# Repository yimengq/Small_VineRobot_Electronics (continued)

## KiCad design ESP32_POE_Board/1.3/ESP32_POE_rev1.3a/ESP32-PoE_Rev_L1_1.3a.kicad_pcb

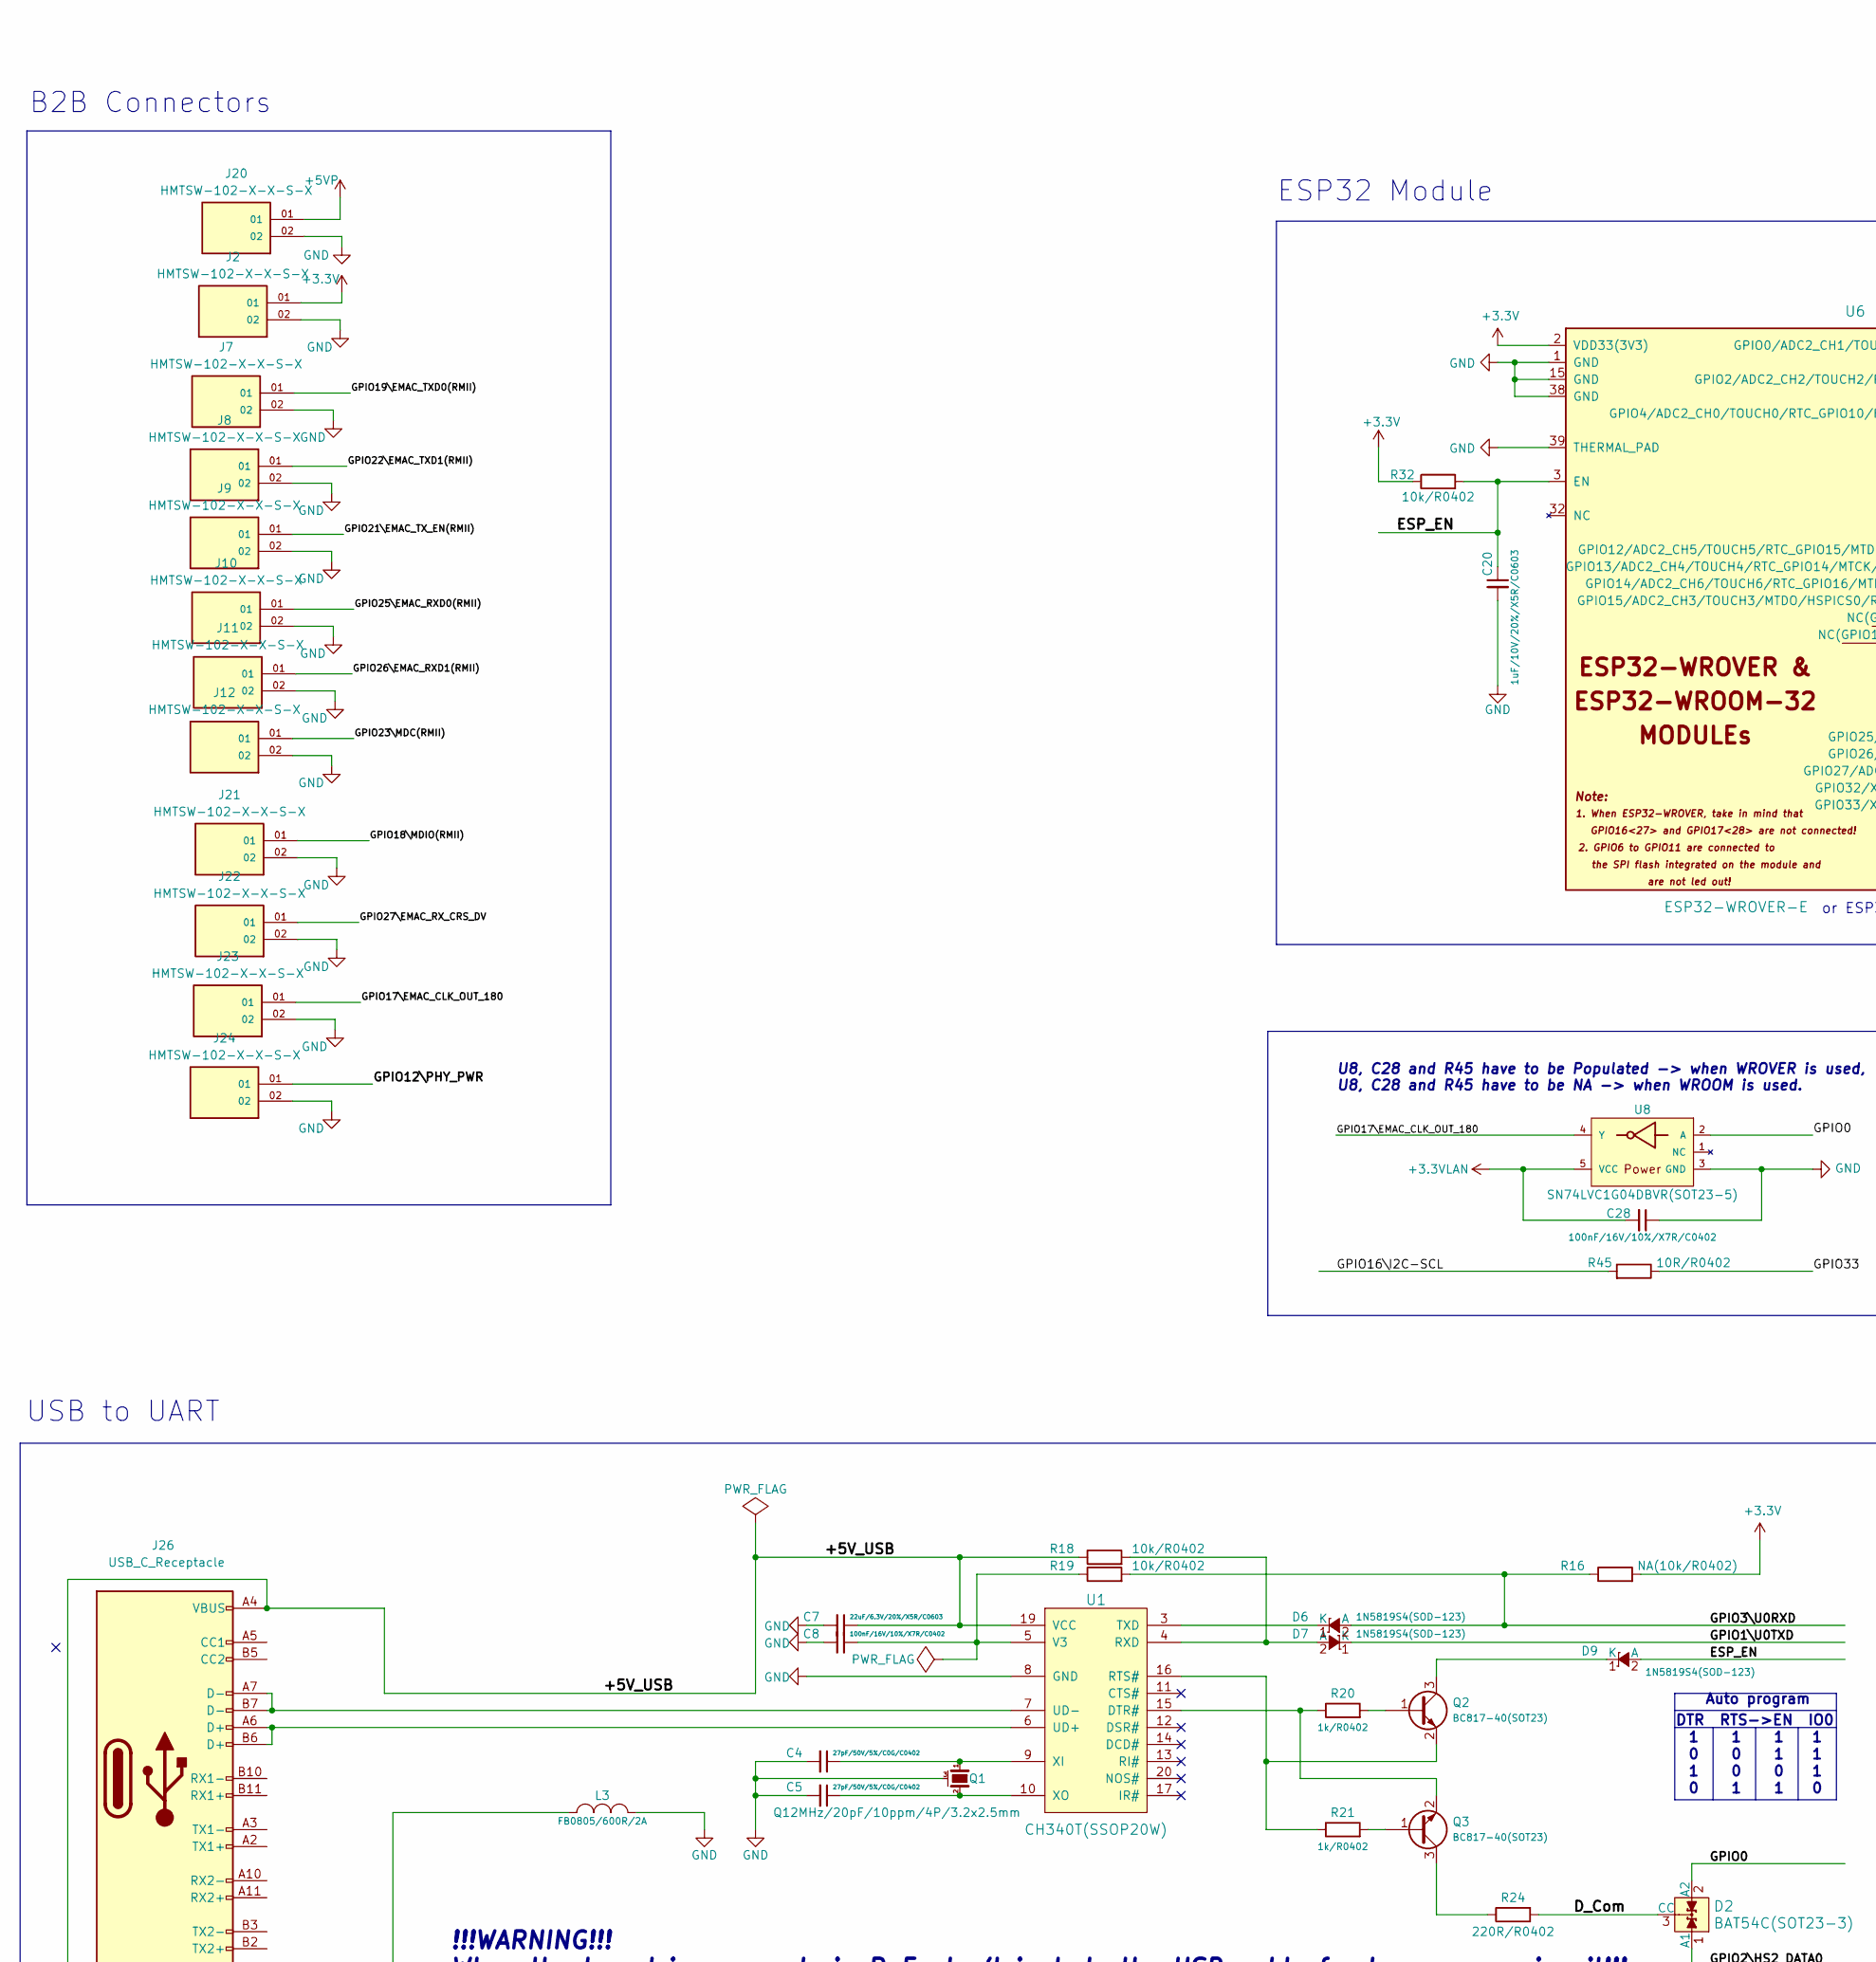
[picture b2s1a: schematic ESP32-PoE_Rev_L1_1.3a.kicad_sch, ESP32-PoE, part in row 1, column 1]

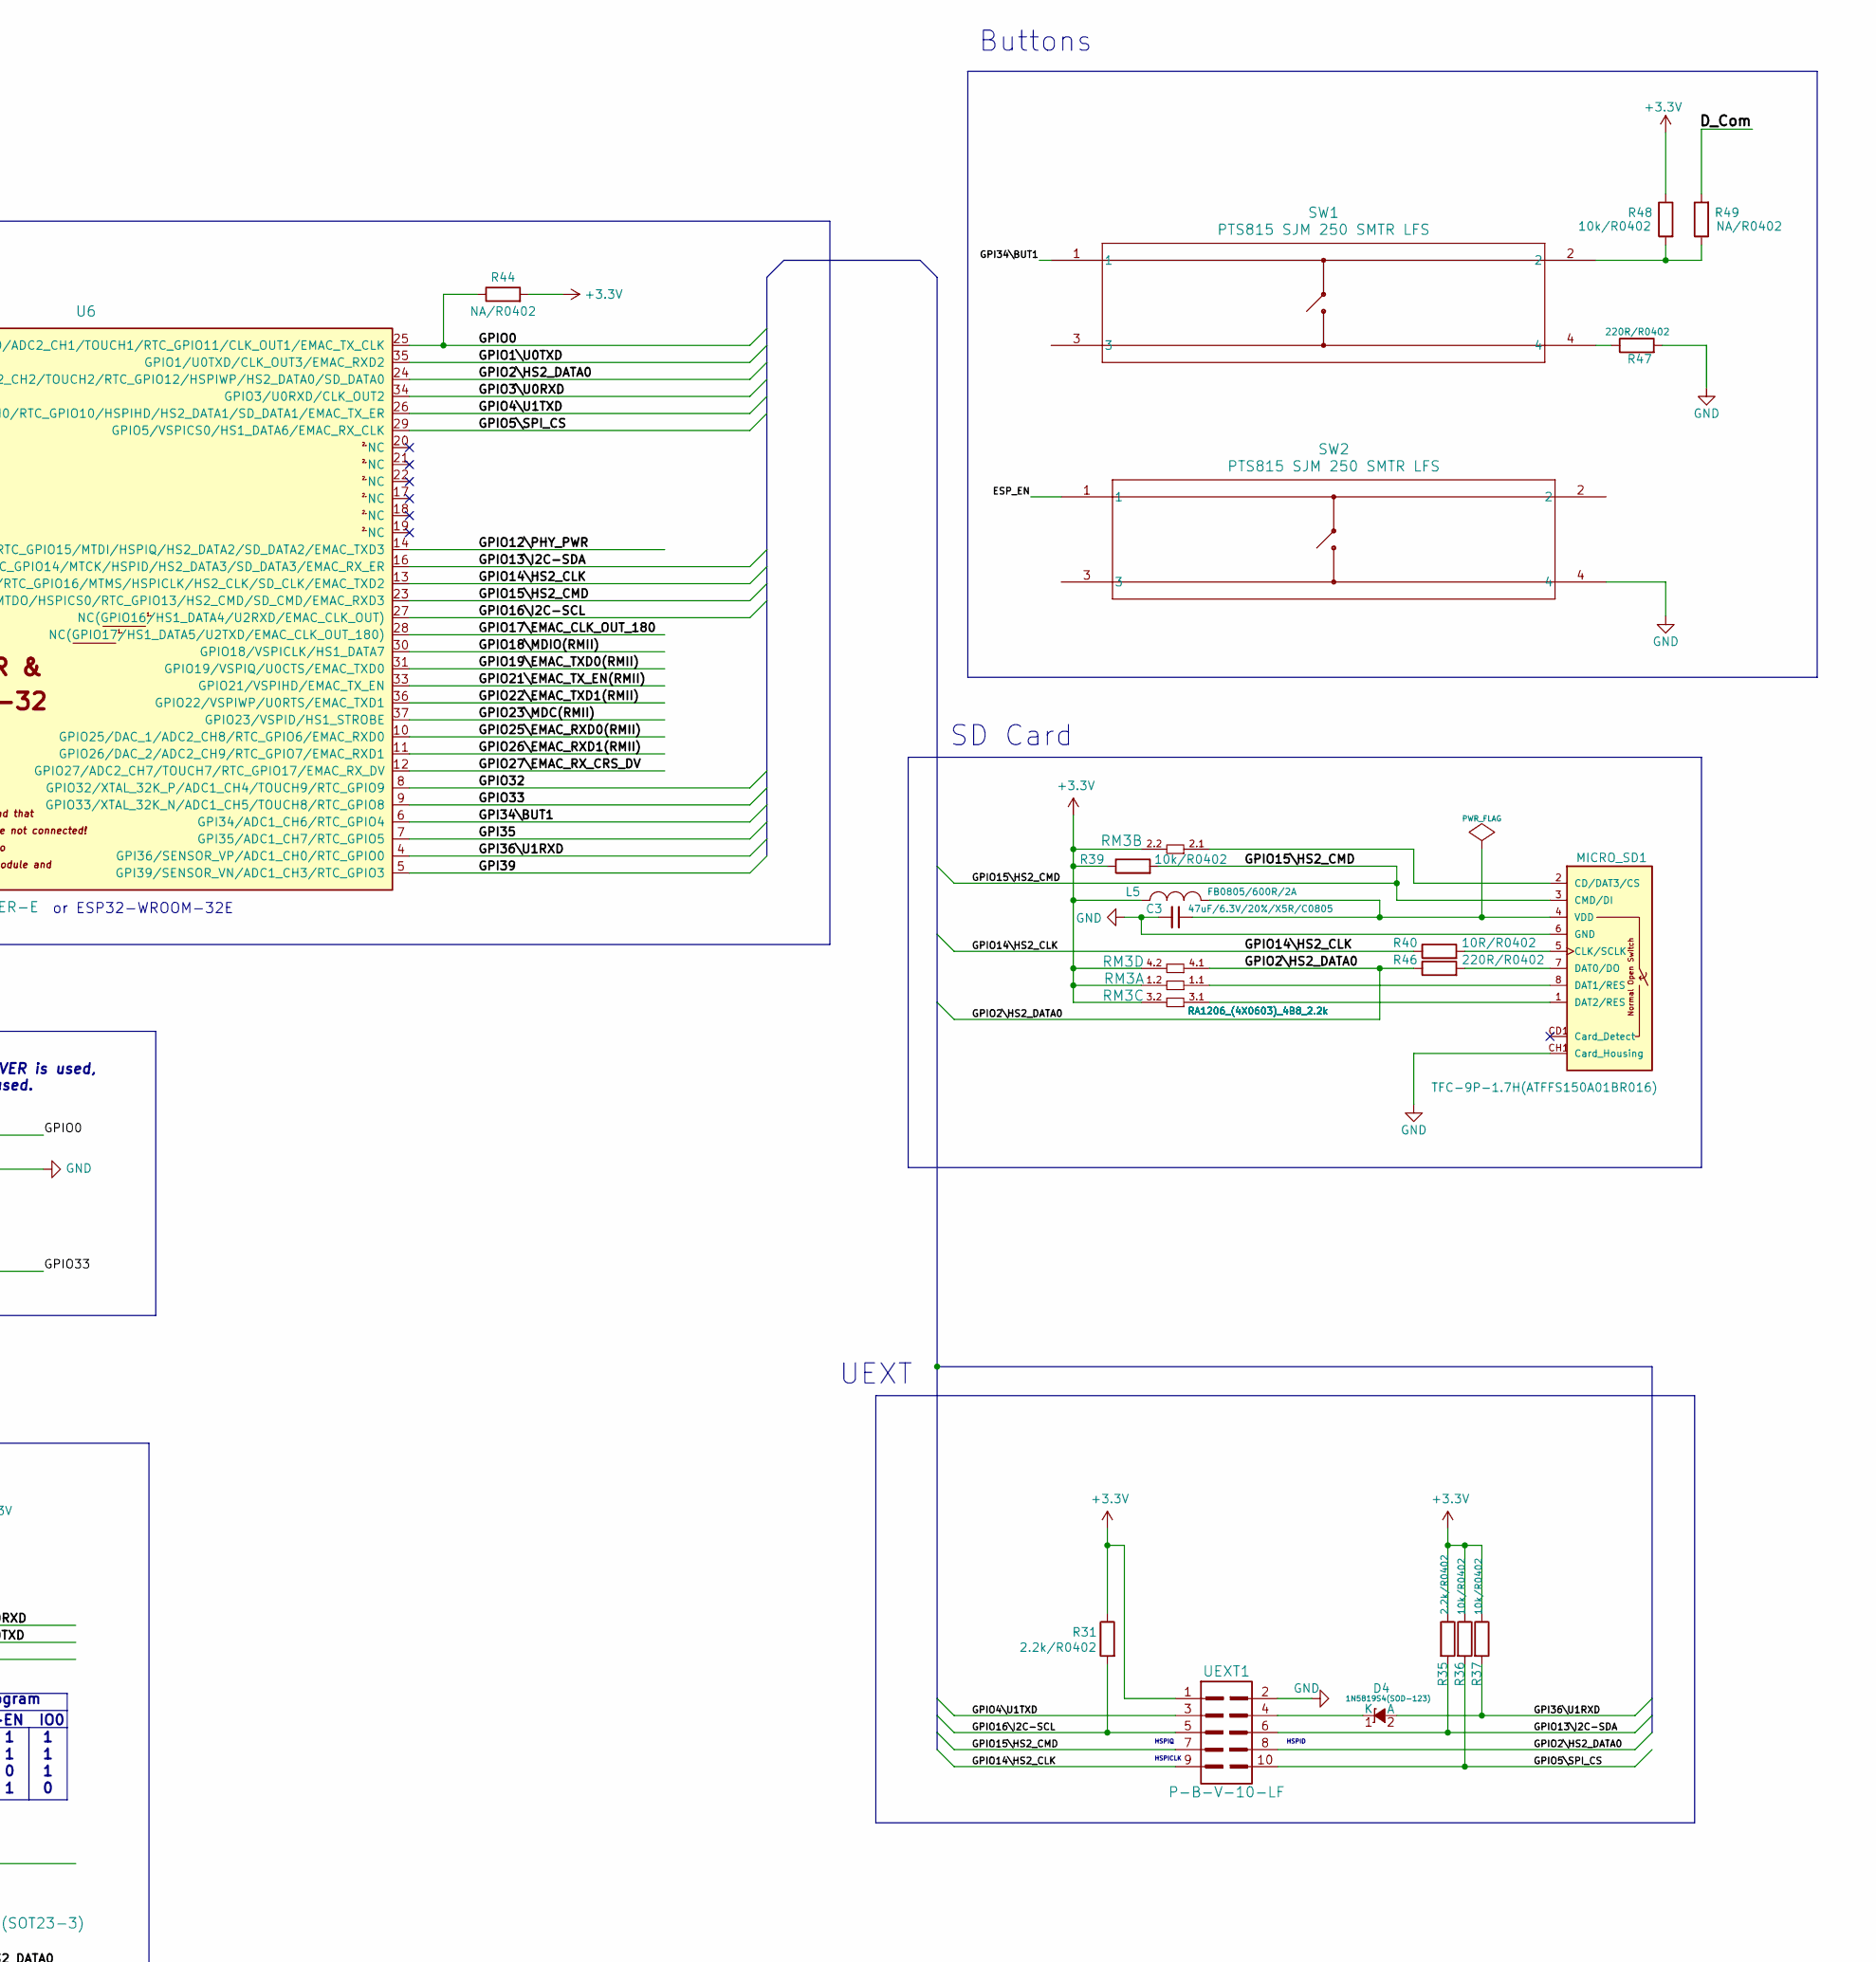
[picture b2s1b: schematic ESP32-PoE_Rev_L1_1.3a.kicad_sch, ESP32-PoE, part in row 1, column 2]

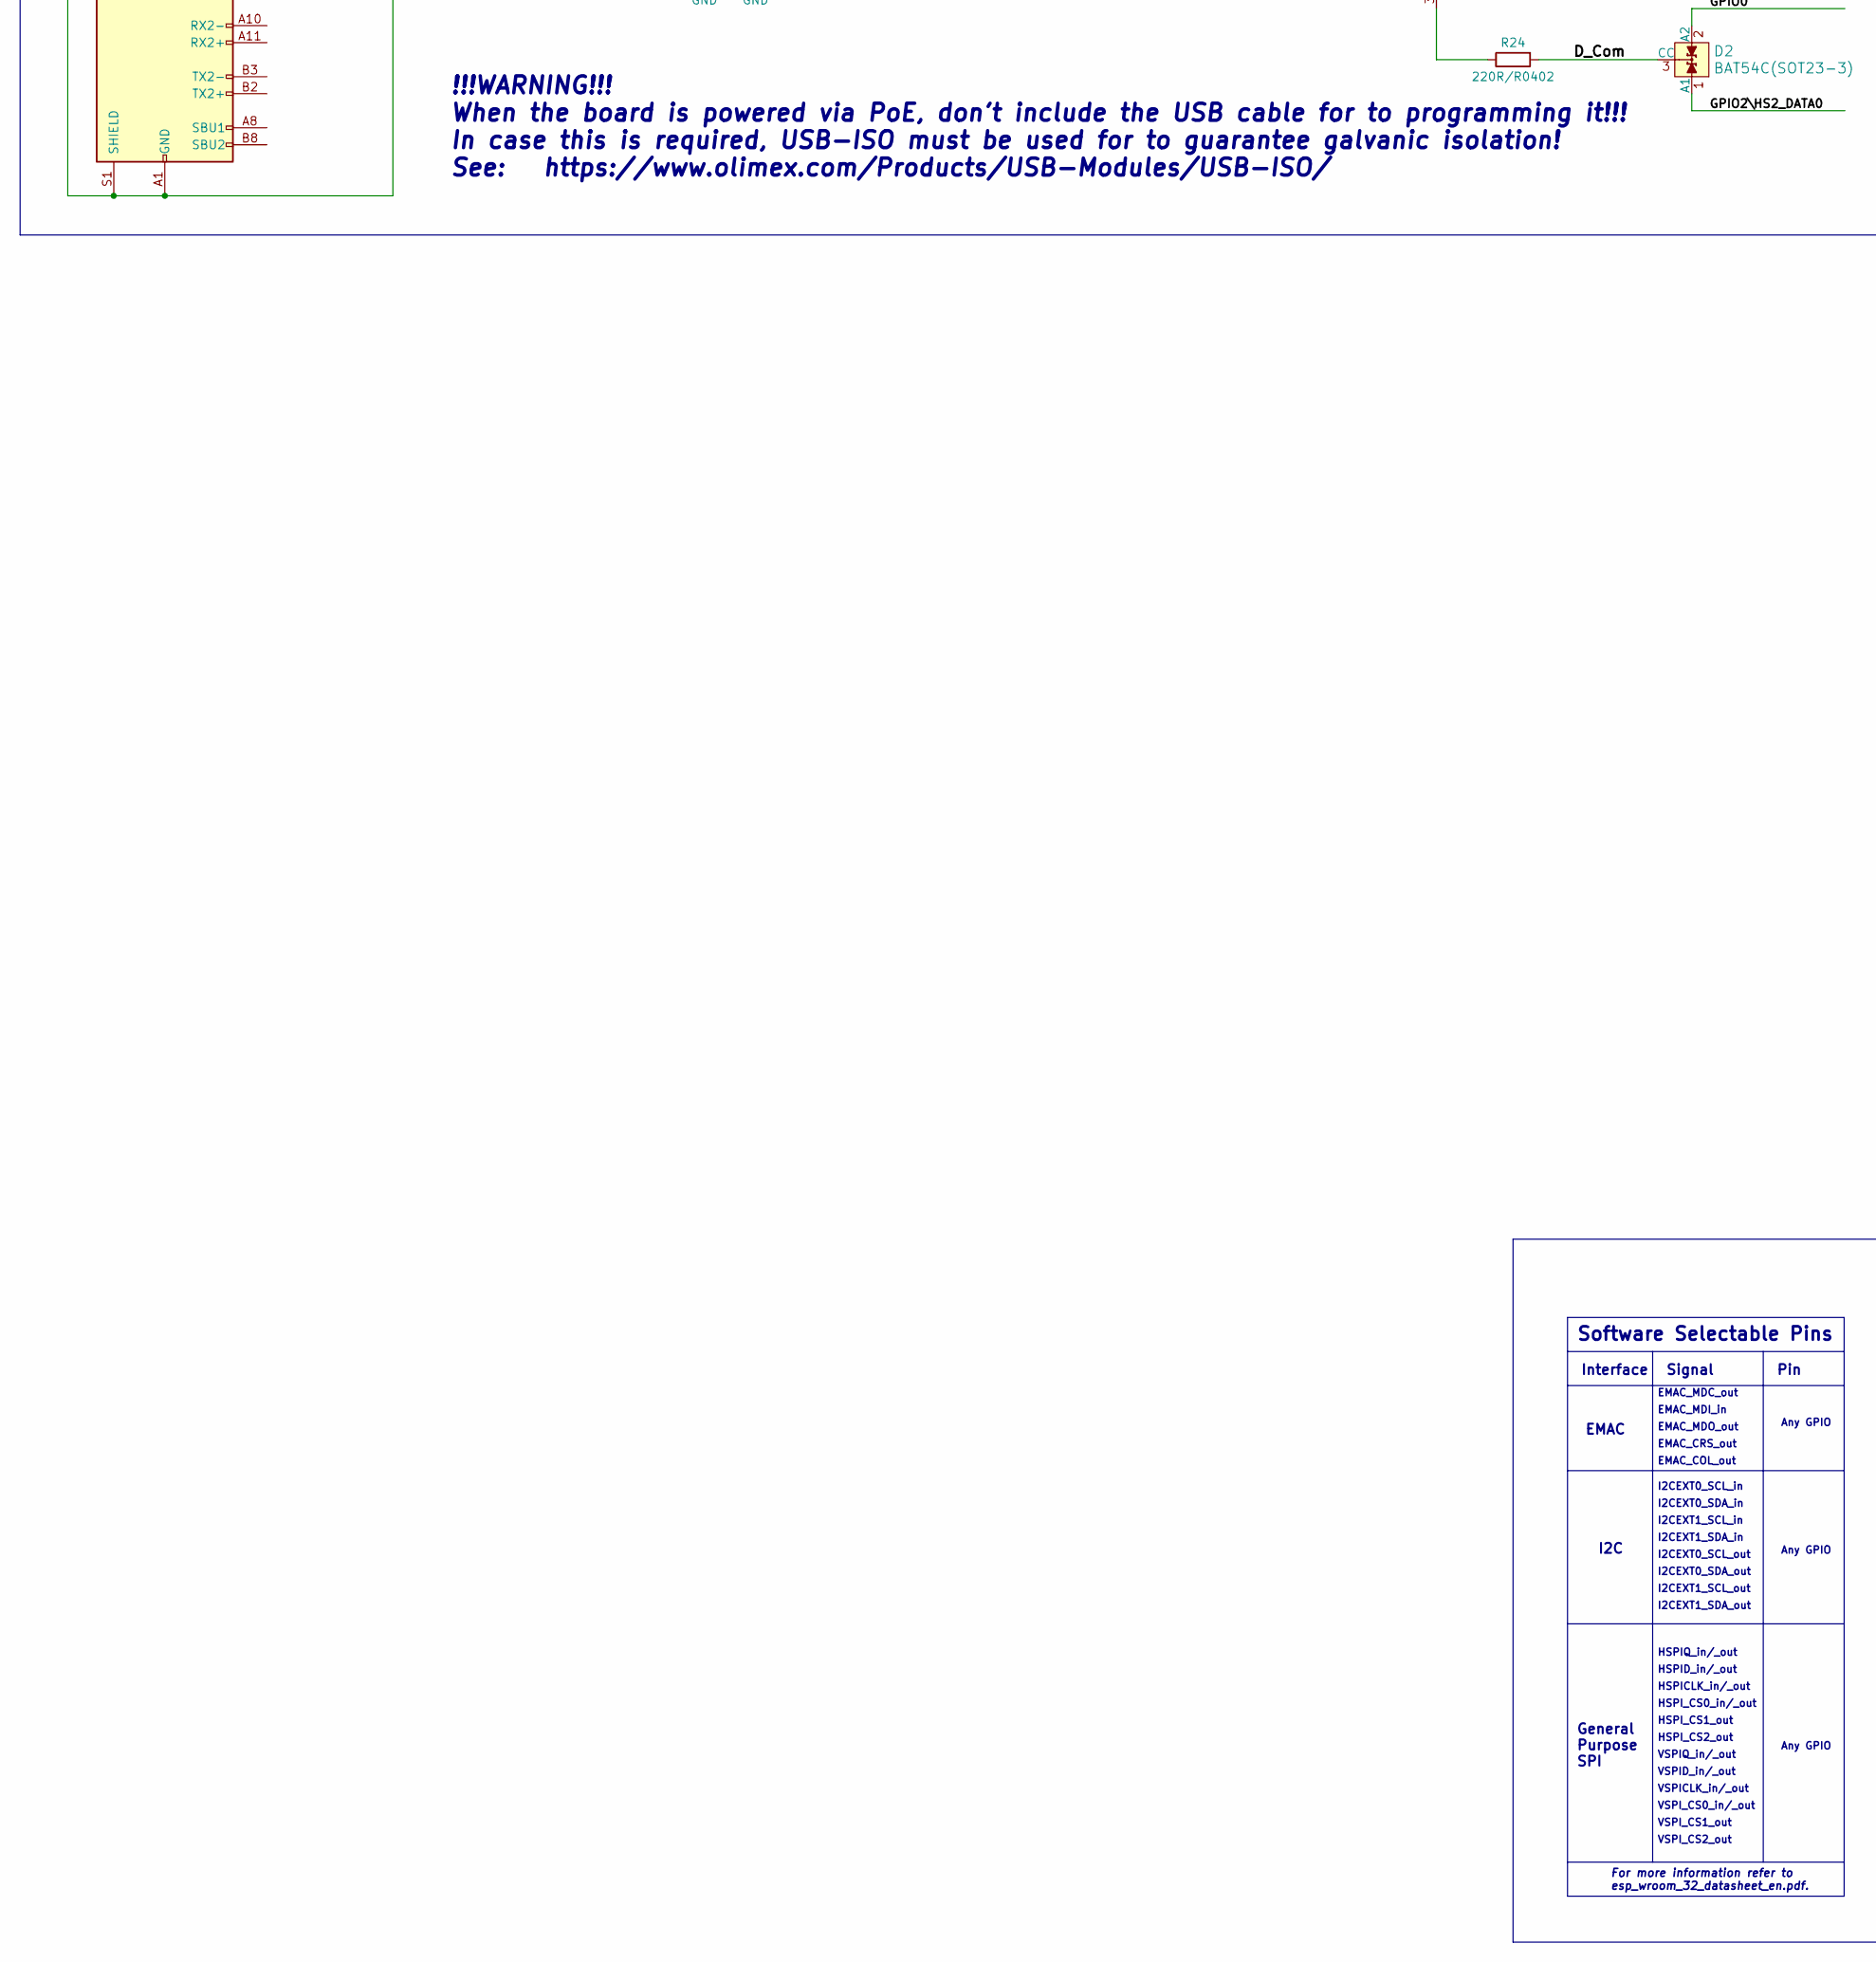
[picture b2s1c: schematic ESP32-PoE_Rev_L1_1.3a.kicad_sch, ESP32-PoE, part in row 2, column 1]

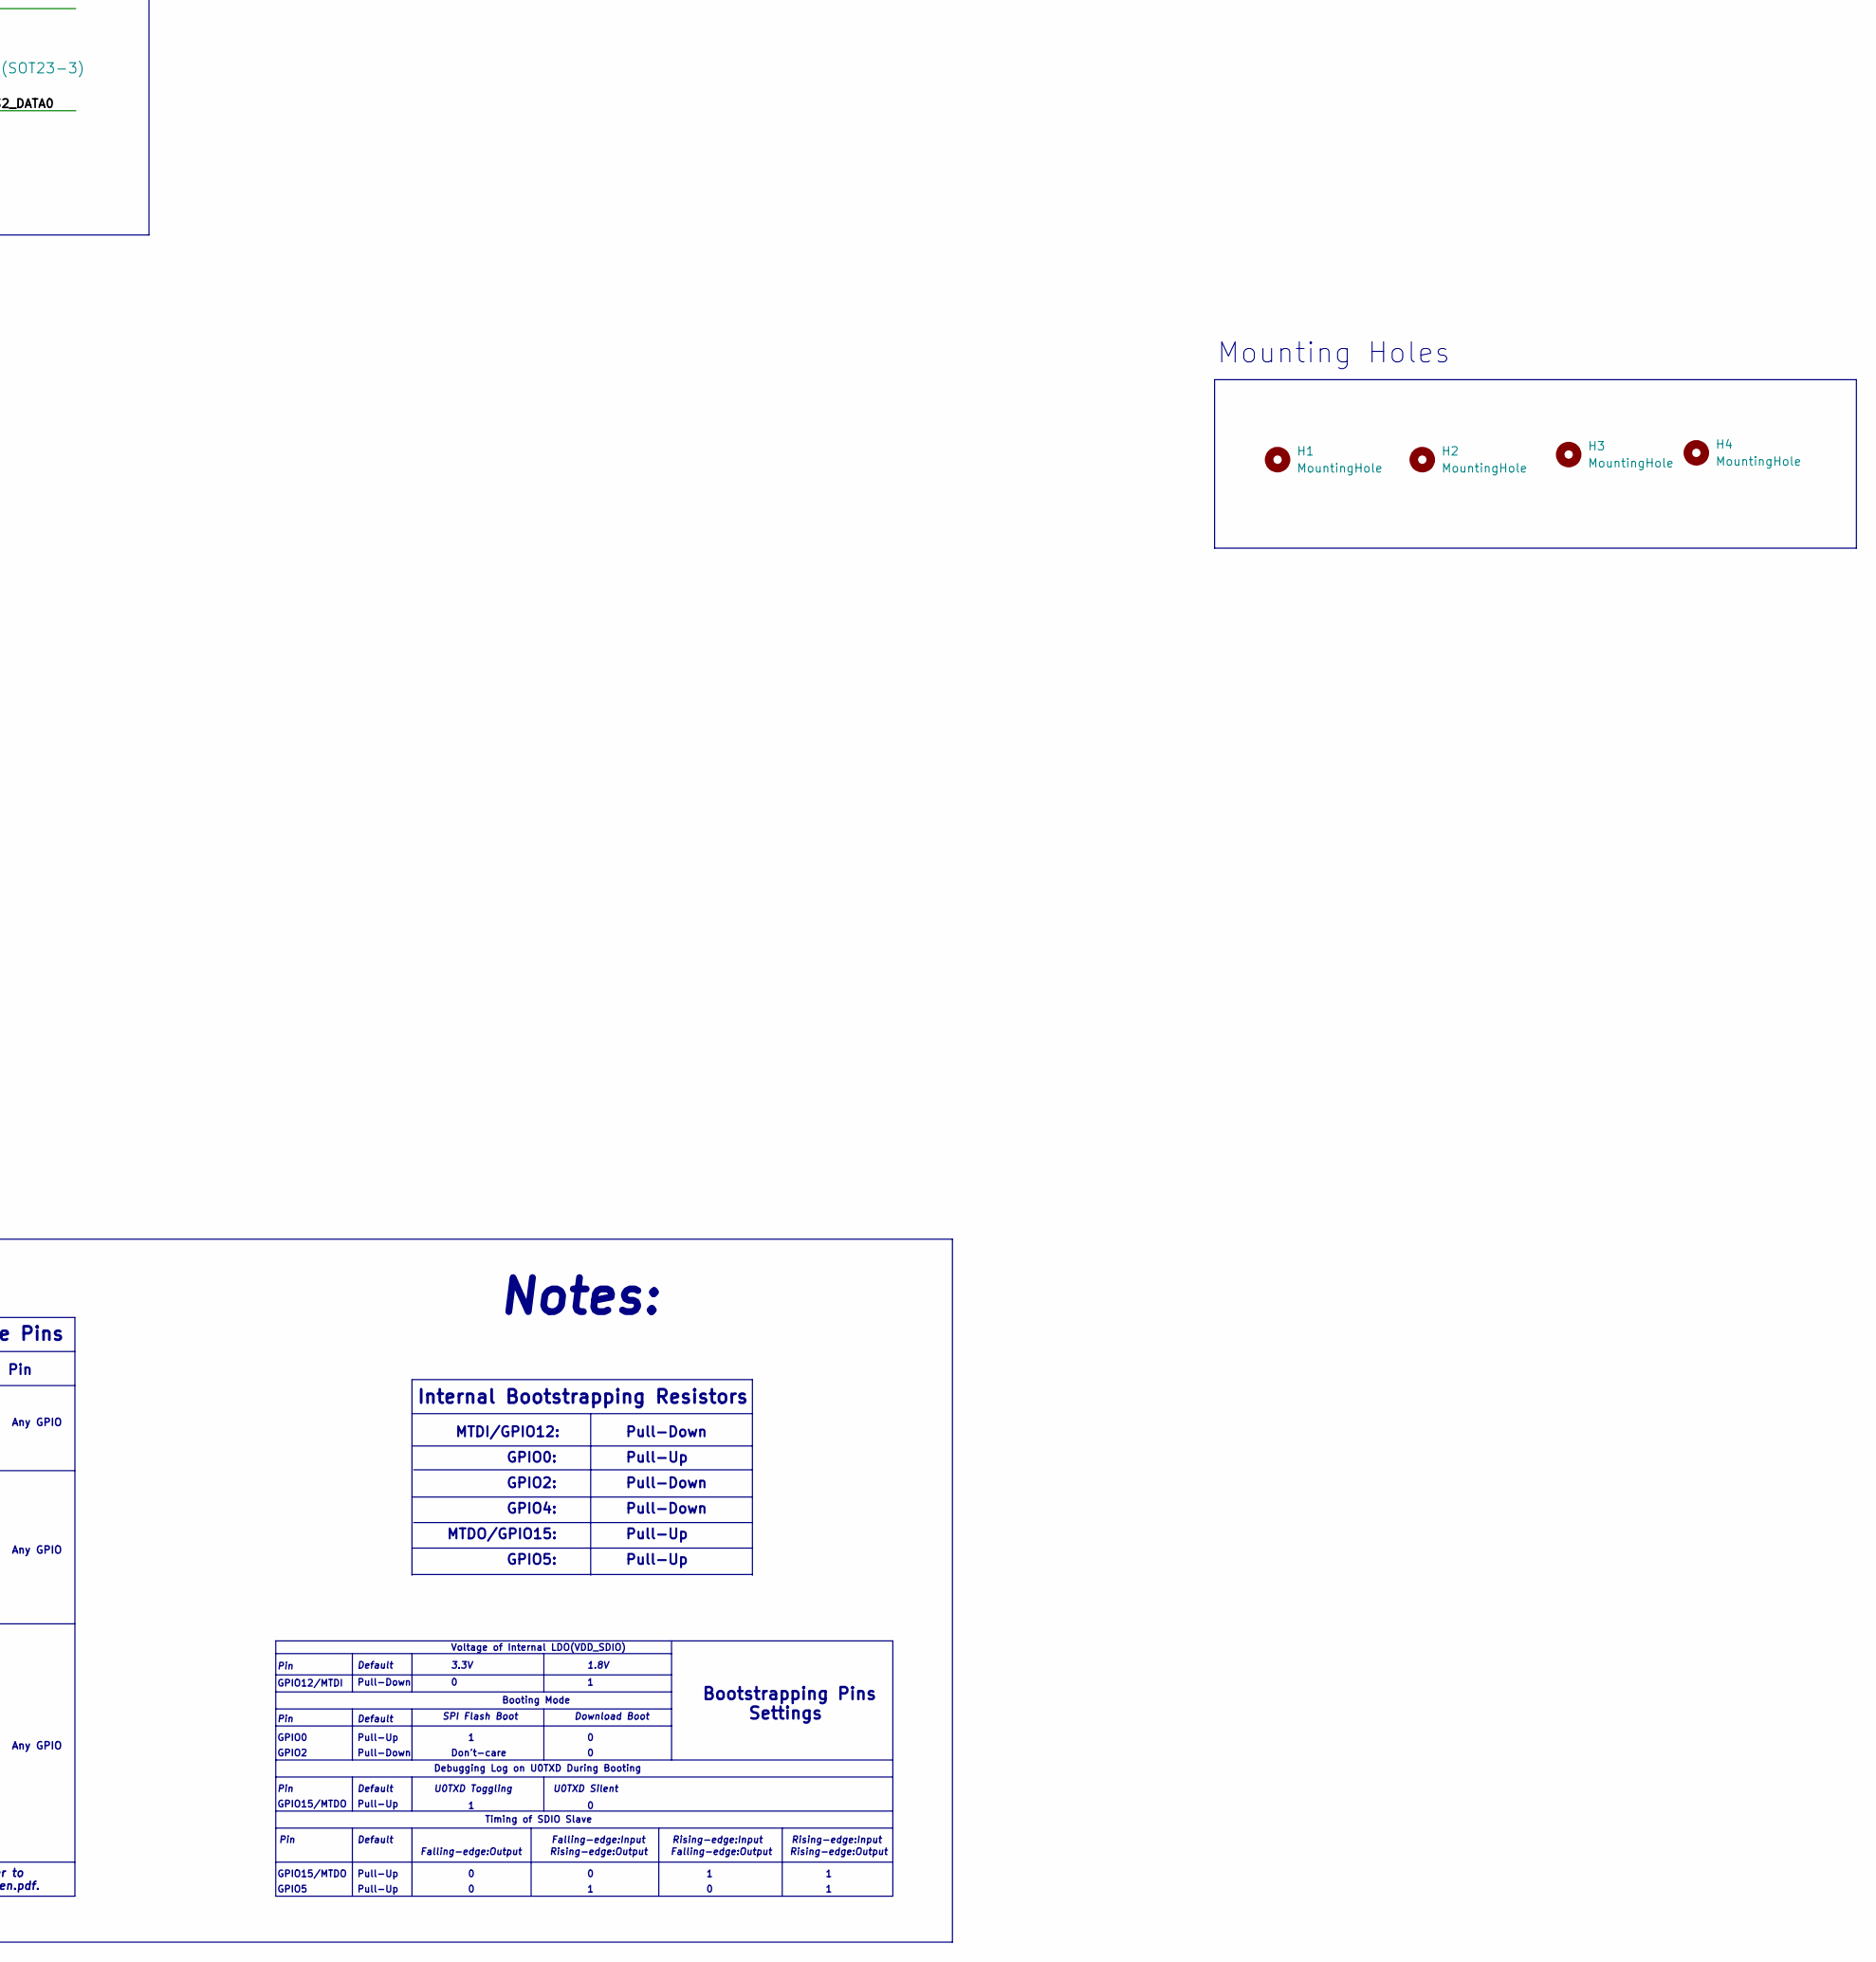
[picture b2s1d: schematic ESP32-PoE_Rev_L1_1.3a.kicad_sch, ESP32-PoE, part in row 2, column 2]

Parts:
C3: 47uF/6.3V/20%/X5R/C0805; C_0805_5MIL_DWS
C4, C5: 27pF/50V/5%/C0G/C0402; C_0402_5MIL_DWS
C7: 22uF/6.3V/20%/X5R/C0603; C_0603_5MIL_DWS
C8, C28: 100nF/16V/10%/X7R/C0402; C_0402_5MIL_DWS
C20: 1uF/10V/20%/X5R/C0603; C_0603_5MIL_DWS
D2: BAT54C(SOT23-3); SOT23-3
D4, D6, D7, D9: 1N5819S4(SOD-123); SOD-123_1C-2A_KA
H1, H2, H3, H4: MountingHole; MountingHole_2.1mm
J2, J7, J8, J9, J10, J11, J12, J20, J21, J22, J23, J24: HMTSW-102-X-X-S-X; SAMTEC_HMTSW-102-X-X-S-X; PARTREV A
J26: USB_C_Receptacle; USB_C_Receptacle_Molex_105450-0101-L
L3, L5: FB0805/600R/2A; L_0805_5MIL_DWS
MICRO_SD1: TFC-9P-1.7H(ATFFS150A01BR016); uSD(TFC-9P-1.xH(ATFFS150A01BR016))
Q1: Q12MHz/20pF/10ppm/4P/3.2x2.5mm; TSX-3.2x2.5mm_GND(3)
Q2, Q3: BC817-40(SOT23); SOT23
R16: NA(10k/R0402); R_0402_5MIL_DWS
R18, R19, R32, R36, R37, R39, R48: 10k/R0402; R_0402_5MIL_DWS
R20, R21: 1k/R0402; R_0402_5MIL_DWS
R24, R46, R47: 220R/R0402; R_0402_5MIL_DWS
R31, R35: 2.2k/R0402; R_0402_5MIL_DWS
R40, R45: 10R/R0402; R_0402_5MIL_DWS
R44, R49: NA/R0402; R_0402_5MIL_DWS
RM3: RA1206_(4X0603)_4B8_2.2k; R_MATRIX_4
SW1, SW2: PTS815 SJM 250 SMTR LFS; SW4_PTS815 SJM 250 SMTR LFS_CNK
U1: CH340T(SSOP20W); SSOP-20W
U6: ESP32-WROVER-E; ESP32-WROVER(WROOM)-UNIVERSAL_MODULE
U8: SN74LVC1G04DBVR(SOT23-5); SOT-23-5
UEXT1: P-B-V-10-LF; GBH-254-SMT-10

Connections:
+3.3V: J2.01, L5.1, R16.2, R31.1, R32.1, R35.1, R36.1, R37.1, R39.1, R44.2, R48.1, RM3.1.2, RM3.2.2, RM3.3.2, RM3.4.2, U6.2 (VDD33(3V3)), UEXT1.1
+3.3VLAN: C28.2, U8.5 (VCC)
+5VP: J20.01
/+5V_USB: C7.1, J26.A1 (GND), J26.A4 (VBUS), J26.A9 (VBUS), J26.A12 (GND), J26.B1 (GND), J26.B4 (VBUS), J26.B9 (VBUS), J26.B12 (GND), J26.S1 (SHIELD), L3.1, R18.1, U1.19 (VCC)
/D_Com: D2.3 (CC), R24.2, R49.2
/ESP_EN: C20.1, D9.2 (A), R32.2, SW2.1, U6.3 (EN)
/GPI34\BUT1: SW1.1, U6.6 (GPI34/ADC1_CH6/RTC_GPIO4)
/GPI35: U6.7 (GPI35/ADC1_CH7/RTC_GPIO5)
/GPI36\U1RXD: D4.2 (A), R37.2, U6.4 (GPI36/SENSOR_VP/ADC1_CH0/RTC_GPIO0)
/GPI39: U6.5 (GPI39/SENSOR_VN/ADC1_CH3/RTC_GPIO3)
/GPIO0: D2.2 (A2), R44.1, U6.25 (GPIO0/ADC2_CH1/TOUCH1/RTC_GPIO11/CLK_OU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), U8.2 (A)
/GPIO1\U0TXD: D7.1 (K), U6.35 (GPIO1/U0TXD/CLK_OUT3/EMAC_RXD2)
/GPIO2\HS2_DATA0: D2.1 (A1), R46.1, RM3.4.1, U6.24 (GPIO2/ADC2_CH2/TOUCH2/RTC_GPIO12/HSPIWP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), UEXT1.8
/GPIO3\U0RXD: D6.2 (A), R16.1, R19.2, U6.34 (GPIO3/U0RXD/CLK_OUT2)
/GPIO4\U1TXD: U6.26 (GPIO4/ADC2_CH0/TOUCH0/RTC_GPIO10/HSPIHD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), UEXT1.3
/GPIO5\SPI_CS: R36.2, U6.29 (GPIO5/VSPICS0/HS1_DATA6/EMAC_RX_CLK), UEXT1.10
/GPIO12\PHY_PWR: J24.01, U6.14 (GPIO12/ADC2_CH5/TOUCH5/RTC_GPIO15/MTDI/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)
/GPIO13\I2C-SDA: R35.2, U6.16 (GPIO13/ADC2_CH4/TOUCH4/RTC_GPIO14/MTCK/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), UEXT1.6
/GPIO14\HS2_CLK: R40.1, U6.13 (GPIO14/ADC2_CH6/TOUCH6/RTC_GPIO16/MTMS/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), UEXT1.9
/GPIO15\HS2_CMD: MICRO_SD1.3 (CMD/DI), R39.2, U6.23 (GPIO15/ADC2_CH3/TOUCH3/MTDO/HSPICS0/RTC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), UEXT1.7
/GPIO16\I2C-SCL: R31.2, R45.2, U6.27 (NC(GPIO16/HS1_DATA4/U2RXD/EMAC_CLK_OUT)), UEXT1.5
/GPIO17\EMAC_CLK_OUT_180: J23.01, U6.28 (NC(GPIO17/HS1_DATA5/U2TXD/EMAC_CLK_OUT_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), U8.4 (Y)
/GPIO18\MDIO(RMII): J21.01, U6.30 (GPIO18/VSPICLK/HS1_DATA7)
/GPIO19\EMAC_TXD0(RMII): J7.01, U6.31 (GPIO19/VSPIQ/U0CTS/EMAC_TXD0)
/GPIO21\EMAC_TX_EN(RMII): J9.01, U6.33 (GPIO21/VSPIHD/EMAC_TX_EN)
/GPIO22\EMAC_TXD1(RMII): J8.01, U6.36 (GPIO22/VSPIWP/U0RTS/EMAC_TXD1)
/GPIO23\MDC(RMII): J12.01, U6.37 (GPIO23/VSPID/HS1_STROBE)
/GPIO25\EMAC_RXD0(RMII): J10.01, U6.10 (GPIO25/DAC_1/ADC2_CH8/RTC_GPIO6/EMAC_RX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)
/GPIO26\EMAC_RXD1(RMII): J11.01, U6.11 (GPIO26/DAC_2/ADC2_CH9/RTC_GPIO7/EMAC_RX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)
/GPIO27\EMAC_RX_CRS_DV: J22.01, U6.12 (GPIO27/ADC2_CH7/TOUCH7/RTC_GPIO17/EMAC_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)
/GPIO32: U6.8 (GPIO32/XTAL_32K_P/ADC1_CH4/TOUCH9/RTC_G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)
/GPIO33: R45.1, U6.9 (GPIO33/XTAL_32K_N/ADC1_CH5/TOUCH8/RTC_G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)
GND: C3.2, C4.2, C5.2, C7.2, C8.2, C20.2, C28.1, J2.02, J7.02, J8.02, J9.02, J10.02, J11.02, J12.02, J20.02, J21.02, J22.02, J23.02, J24.02, L3.2, MICRO_SD1.6 (GND), MICRO_SD1.CH1 (Card_Housing), Q1.3 (case), R47.2, SW2.4, U1.8 (GND), U6.1 (GND), U6.15 (GND), U6.38 (GND), U6.39 (THERMAL_PAD), U8.3 (GND), UEXT1.2
unnamed: D4.1 (K), UEXT1.4
unnamed: D6.1 (K), U1.3 (TXD)
unnamed: D7.2 (A), R18.2, U1.4 (RXD)
unnamed: D9.1 (K), Q2.3 (C)
unnamed: MICRO_SD1.2 (CD/DAT3/CS), RM3.2.1
unnamed: MICRO_SD1.5 (CLK/SCLK), R40.2
unnamed: MICRO_SD1.7 (DAT0/DO), R46.2
unnamed: MICRO_SD1.8 (DAT1/RES), RM3.1.1
unnamed: MICRO_SD1.1 (DAT2/RES), RM3.3.1
unnamed: C3.1, L5.2, MICRO_SD1.4 (VDD)
unnamed: Q2.1 (B), R20.2
unnamed: Q2.2 (E), R21.1, U1.16 (RTS#)
unnamed: Q3.1 (B), R21.2
unnamed: Q3.3 (C), R24.1
unnamed: Q3.2 (E), R20.1, U1.15 (DTR#)
unnamed: R47.1, SW1.4
unnamed: R48.2, R49.1, SW1.2
unnamed: J26.A6 (D+), J26.B6 (D+), U1.6 (UD+)
unnamed: J26.A7 (D-), J26.B7 (D-), U1.7 (UD-)
unnamed: C8.1, R19.1, U1.5 (V3)
unnamed: C4.1, Q1.1, U1.9 (XI)
unnamed: C5.1, Q1.2, U1.10 (XO)

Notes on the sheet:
Pin
SD Card
Pull-Down
Buttons
I2CEXT0_SCL_out
I2CEXT1_SDA_in
VSPID_in/_out
EMAC_COL_out
UEXT
Any GPIO
Rising-edge:Output
GPIO5:
Download Boot
HSPICLK_in/_out
VSPIQ_in/_out
Signal
Falling-edge:Output
HSPID_in/_out
Voltage of Internal LDO(VDD_SDIO)
GPIO2:
Interface
EMAC_MDI_in
General Purpose SPI
Debugging Log on U0TXD During Booting
I2CEXT1_SCL_in
Default
I2CEXT0_SCL_in
USB to UART
Pull-Up
U0TXD Toggling
3.3V
HSPIQ
EMAC_MDO_out
Falling-edge:Input
HSPICLK
GPIO4:
VSPI_CS0_in/_out
B2B Connectors
U8, C28 and R45 have to be Populated -> when WROVER is used, U8, C28 and R45 have to be NA -> when WROOM is used.
DTR RTS->EN IO0

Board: 4 copper layers, 59 parts (25 on the bottom side), 51 nets, no tracks yet.
